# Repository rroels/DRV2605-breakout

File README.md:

# DRV2605 Breakout Board

> [!WARNING]
> The information and material (code, designs, files, ...) are provided "AS IS". We make no representation or warranty of any kind, express or implied, regarding the accuracy, adequacy, validity, reliability, availability, or completeness of any information or material. Use this at your own risk.

> [!WARNING]
> At the time of writing this PCB has not even been produced yet, and as such, it has not even been tested yet! Once it has been properly tested, I will confirm that everything works as expected.

## Introduction

This is a breakout board for the TI DRV2605 Haptic Motor Driver. 

[https://www.ti.com/product/DRV2605L](https://www.ti.com/product/DRV2605L)

## Change Log

* v1.0
  * Initial design 

## Design Considerations

* This board is for the DRV2605L variant, VSSOP package

## Schematics 

## How to Obtain the Physical PCB

The Gerber file is in this repository (`gerbers/DRV2605-breakout.zip`). Simply upload this file a PCB manufacturer of your choice (JLPCB, PCBWay, ...), and you they will make it for you for as low as \$5 for 5 pieces (with the cheapest shipping option, which can take a few weeks).

For JLCPCB, select the order number option where they will replace "JLCJLCJLCJLC" on the board with the actual order number.

> [!WARNING]
> Note that will still have to solder the components onto the PCB yourself!

## How to Edit Design

Everything you need to edit this design in KiCad 8 is included in the repository.

## Sources

* [https://www.ti.com/product/DRV2605L](https://www.ti.com/product/DRV2605L)
* [https://www.adafruit.com/product/2305](https://www.adafruit.com/product/2305)
* [https://www.sparkfun.com/products/14538](https://www.sparkfun.com/products/14538)

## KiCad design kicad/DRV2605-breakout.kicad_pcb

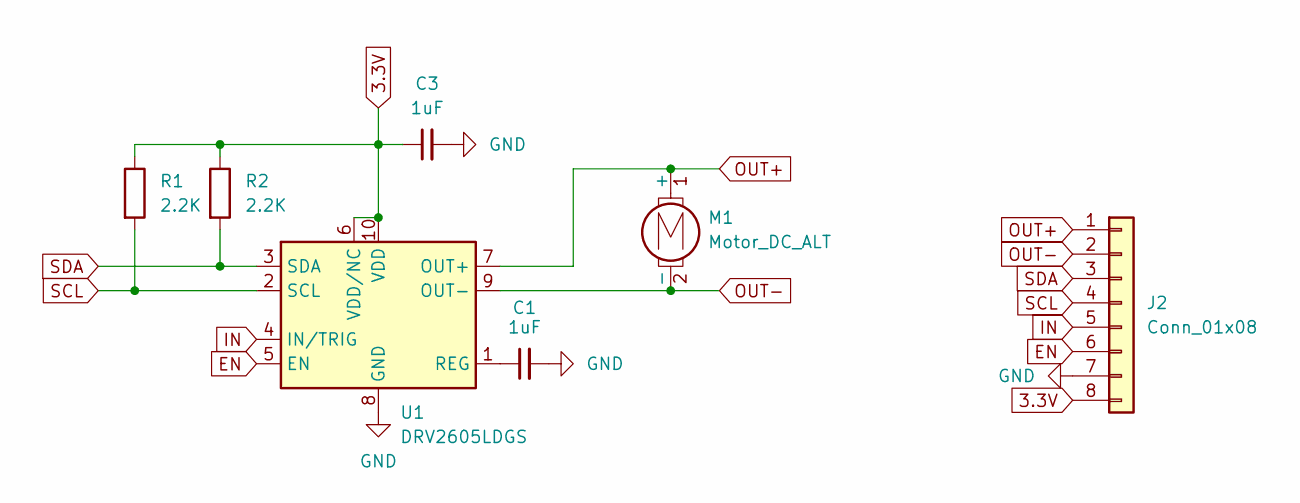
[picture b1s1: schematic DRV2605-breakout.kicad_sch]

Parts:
C1, C3: 1uF; C_0603_1608Metric_Pad1.08x0.95mm_HandSolder
J2: Conn_01x08; PinHeader_1x08_P2.54mm_Vertical
M1: Motor_DC_ALT; PinHeader_1x02_P2.54mm_Vertical
R1, R2: 2.2K; R_0603_1608Metric_Pad0.98x0.95mm_HandSolder
U1: DRV2605LDGS; VSSOP-10_3x3mm_P0.5mm

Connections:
3.3V: C3.1, J2.8, R1.1, R2.1, U1.6 (VDD/NC), U1.10 (VDD)
EN: J2.6, U1.5 (EN)
GND: C1.2, C3.2, J2.7, U1.8 (GND)
IN: J2.5, U1.4 (IN/TRIG)
unnamed: C1.1, U1.1 (REG)
OUT+: J2.1, M1.1 (+), U1.7 (OUT+)
OUT-: J2.2, M1.2 (-), U1.9 (OUT-)
SCL: J2.4, R1.2, U1.2 (SCL)
SDA: J2.3, R2.2, U1.3 (SDA)

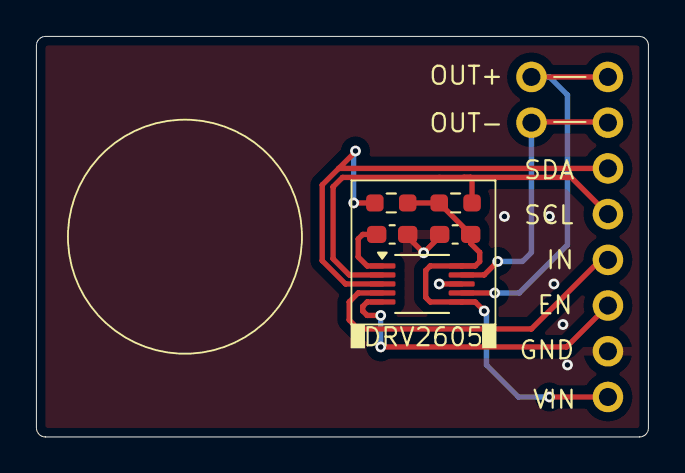
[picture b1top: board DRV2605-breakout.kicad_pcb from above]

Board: 2 copper layers, 34.0 x 22.2 mm, 7 parts (0 on the bottom side), 9 nets.
